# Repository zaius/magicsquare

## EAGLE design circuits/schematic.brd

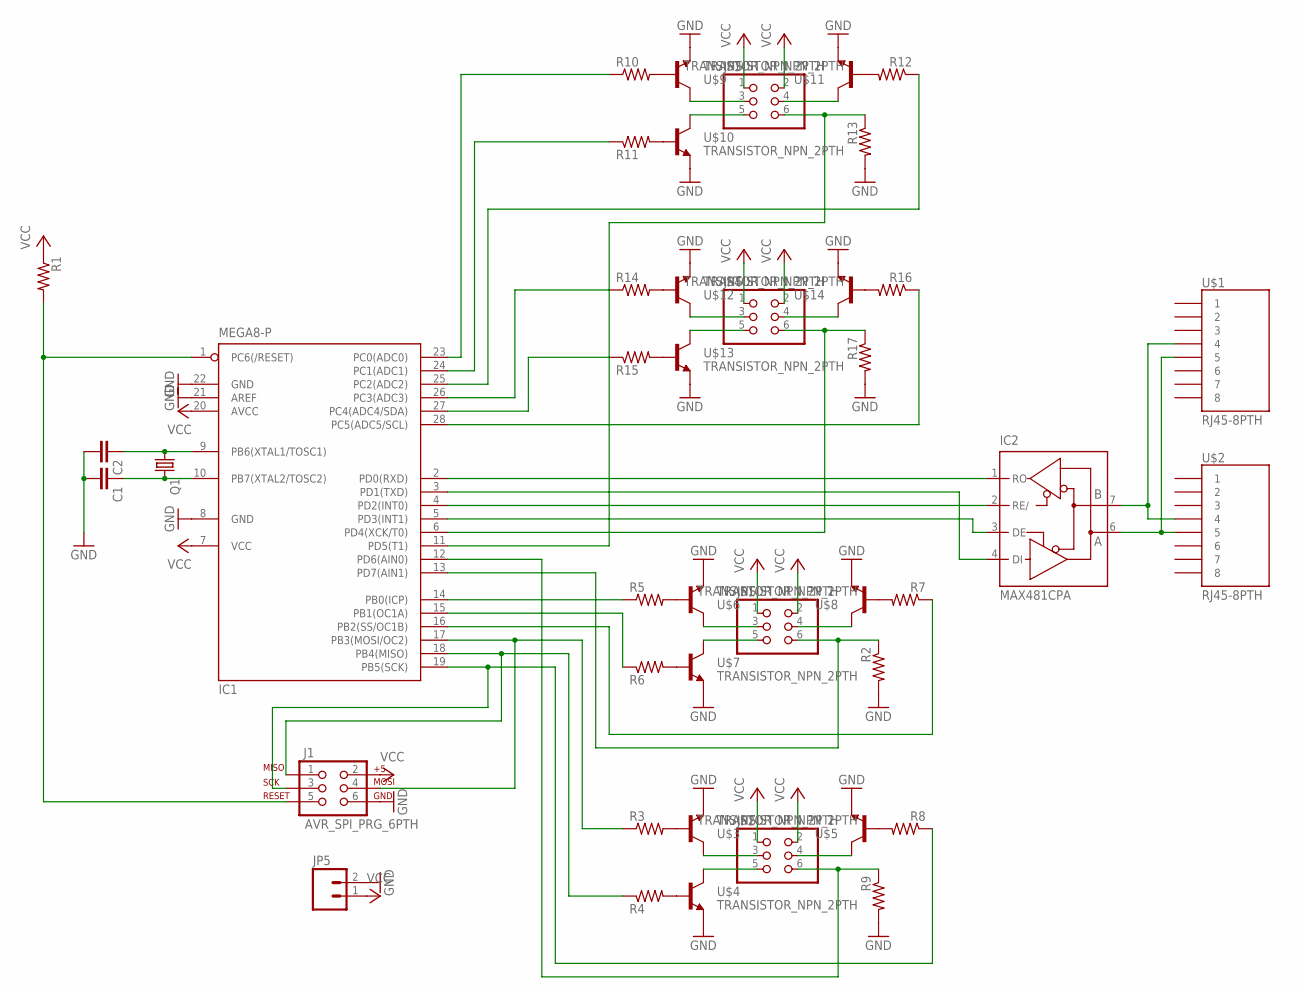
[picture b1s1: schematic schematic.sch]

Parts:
C1, C2: CAPKIT; CAP-PTH-SMALL-KIT
IC1: MEGA8-P; DIL28-3
IC2: MAX481CPA; DIL08
J1: AVR_SPI_PRG_6PTH; 2X3
JP1, JP2, JP3, JP4: PINHD-2X3; 2X03
JP5: M023.5MM; SCREWTERMINAL-3.5MM-2
Q1: CRYSTALHC49U-V; HC49U-V
R1, R2, R3, R4, R5, R6, R7, R8, R9, R10, R11, R12, R13, R14, R15, R16, R17: RESISTORPTH-1/4W; AXIAL-0.4
U$1, U$2: RJ45-8PTH; RJ45-8
U$3, U$4, U$5, U$6, U$7, U$8, U$9, U$10, U$11, U$12, U$13, U$14: TRANSISTOR_NPN_2PTH; TO-92

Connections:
GND: C1.2, C2.2, IC1.8 (GND), IC1.21 (AREF), IC1.22 (GND), IC2.5 (GND), J1.6, JP5.2, R2.P$2 (2), R9.P$2 (2), R13.P$2 (2), R17.P$2 (2), U$3.3 (E), U$4.3 (E), U$5.3 (E), U$6.3 (E), U$7.3 (E), U$8.3 (E), U$9.3 (E), U$10.3 (E), U$11.3 (E), U$12.3 (E), U$13.3 (E), U$14.3 (E)
unnamed: IC2.7 (B), U$1.4, U$2.4
unnamed: IC2.6 (A), U$1.5, U$2.5
unnamed: IC1.26 (PC3(ADC3)), R14.P$1 (1)
unnamed: C2.1, IC1.9 (PB6(XTAL1/TOSC1)), Q1.1
unnamed: C1.1, IC1.10 (PB7(XTAL2/TOSC2)), Q1.2
unnamed: JP1.3, U$6.1 (C)
unnamed: IC1.2 (PD0(RXD)), IC2.1 (RO)
unnamed: IC1.3 (PD1(TXD)), IC2.4 (DI)
unnamed: JP1.5, U$7.1 (C)
unnamed: JP1.4, U$8.1 (C)
unnamed: IC1.27 (PC4(ADC4/SDA)), R15.P$1 (1)
unnamed: IC1.14 (PB0(ICP)), R5.P$1 (1)
unnamed: IC1.15 (PB1(OC1A)), R6.P$1 (1)
unnamed: IC1.13 (PD7(AIN1)), JP1.6, R2.P$1 (1)
unnamed: IC1.5 (PD3(INT1)), IC2.3 (DE)
unnamed: R5.P$2 (2), U$6.2 (B)
unnamed: IC1.1 (PC6(/RESET)), J1.5, R1.P$2 (2)
unnamed: R6.P$2 (2), U$7.2 (B)
unnamed: R7.P$2 (2), U$8.2 (B)
unnamed: IC1.12 (PD6(AIN0)), JP2.6, R9.P$1 (1)
unnamed: IC1.4 (PD2(INT0)), IC2.2 (RE/)
unnamed: R3.P$2 (2), U$3.2 (B)
unnamed: R4.P$2 (2), U$4.2 (B)
unnamed: R8.P$2 (2), U$5.2 (B)
unnamed: IC1.19 (PB5(SCK)), J1.3, R8.P$1 (1)
unnamed: IC1.16 (PB2(SS/OC1B)), R7.P$1 (1)
unnamed: JP2.3, U$3.1 (C)
unnamed: JP2.5, U$4.1 (C)
unnamed: JP2.4, U$5.1 (C)
unnamed: IC1.11 (PD5(T1)), JP3.6, R13.P$1 (1)
unnamed: R10.P$2 (2), U$9.2 (B)
unnamed: R11.P$2 (2), U$10.2 (B)
unnamed: R12.P$2 (2), U$11.2 (B)
unnamed: IC1.24 (PC1(ADC1)), R11.P$1 (1)
unnamed: IC1.25 (PC2(ADC2)), R12.P$1 (1)
unnamed: JP3.3, U$9.1 (C)
unnamed: JP3.5, U$10.1 (C)
unnamed: JP3.4, U$11.1 (C)
unnamed: IC1.6 (PD4(XCK/T0)), JP4.6, R17.P$1 (1)
unnamed: R14.P$2 (2), U$12.2 (B)
unnamed: R15.P$2 (2), U$13.2 (B)
unnamed: R16.P$2 (2), U$14.2 (B)
unnamed: IC1.23 (PC0(ADC0)), R10.P$1 (1)
unnamed: IC1.28 (PC5(ADC5/SCL)), R16.P$1 (1)
unnamed: JP4.3, U$12.1 (C)
unnamed: JP4.5, U$13.1 (C)
unnamed: JP4.4, U$14.1 (C)
unnamed: IC1.17 (PB3(MOSI/OC2)), J1.4, R3.P$1 (1)
unnamed: IC1.18 (PB4(MISO)), J1.1, R4.P$1 (1)
VCC: IC1.7 (VCC), IC1.20 (AVCC), IC2.8 (VCC), J1.2, JP1.1, JP1.2, JP2.1, JP2.2, JP3.1, JP3.2, JP4.1, JP4.2, JP5.1, R1.P$1 (1)

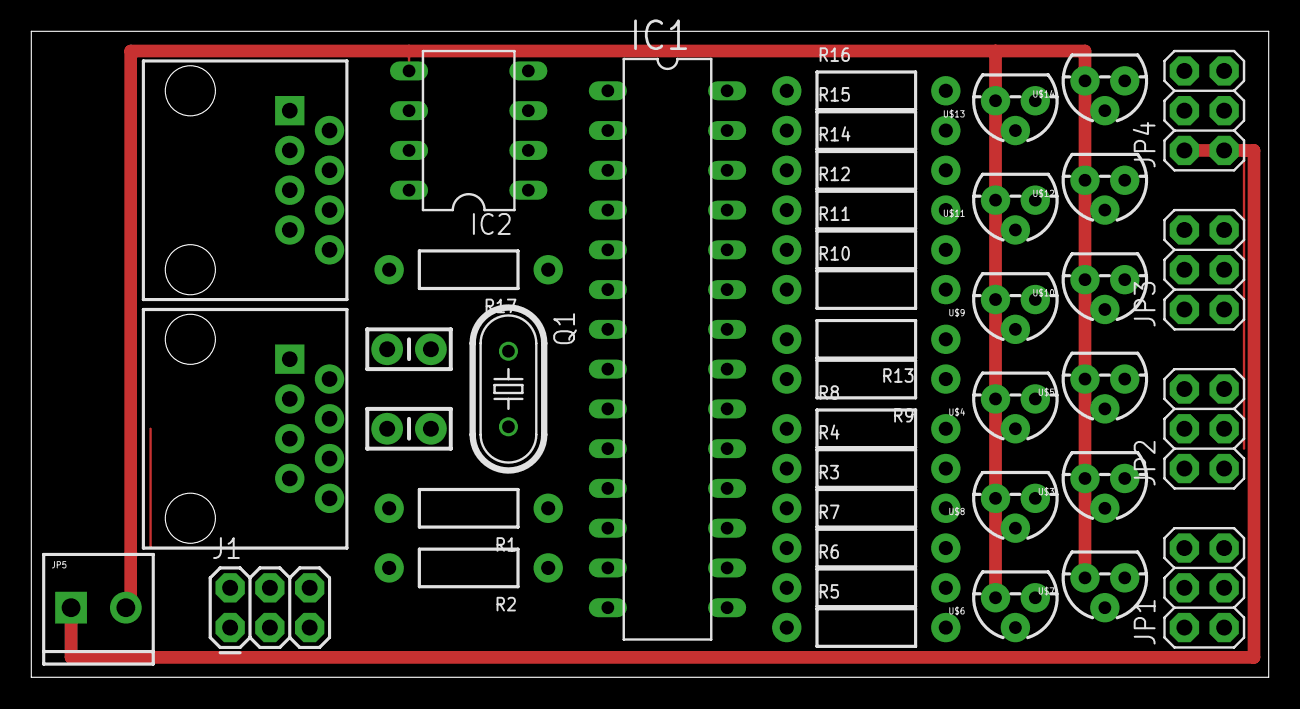
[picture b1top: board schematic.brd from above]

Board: 2 copper layers, 79.0 x 41.3 mm, 42 parts (0 on the bottom side), 51 nets.

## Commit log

2012-05-09 Demo program and makefile.
2012-05-22 Some rough network and switch code.
2012-06-14 Switch multiplexing. LED cycling.
2012-06-18 Use sleep from lib.
2012-06-19 Working switch code.
2012-06-19 Fix switch indexing.
2012-06-26 Untested messaging code.
2012-07-12 Hacked priceless version.
2012-08-06 working proof of concept master with slave simulator in python
2012-08-06 Non-working circuitry.
2012-08-06 Circuit layout v1.
2012-08-06 Right side layout.
2012-08-07 Autorouted, 50 mil, no vias.
2012-08-08 able to infer group orientation in calibration mode and added a function to convert pixel coordinates to button group and button index
2012-08-08 Start of board with custom vcc/gnd lines.
2012-08-08 Self routed version.
2012-08-08 Inverted switch order.
2012-08-08 Fix RJ45 jack footprint.
2012-08-14 Small slave code cleanup.
2012-08-14 Move slave code into subdirectory.
2012-08-16 Proper RGB colors with timers.
2012-08-21 Slave based calibration.
2012-08-21 Simplified slave network.
2012-08-23 master and simulator code for new protocol, but haven't tried running it yet
2012-08-25 Better buffers. Fix makefile.
2012-08-25 added arduino makefile and python file that's supposed to reset the arduino before programming
2012-08-25 arduino reset tweaks
2012-09-07 Fix constant resetting when booting.
2012-09-07 Fix LED ordering to match PCBs.
2012-09-07 Make port pulser use python from path.
2012-09-07 Better fuse rundown.
2012-09-07 RGB cycling in a more readable manner.

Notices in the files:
parts and their libraries:
SparkFun-Connectors: Licensing: CC v3.0 Share-Alike You are welcome to use this library for commercial purposes.
